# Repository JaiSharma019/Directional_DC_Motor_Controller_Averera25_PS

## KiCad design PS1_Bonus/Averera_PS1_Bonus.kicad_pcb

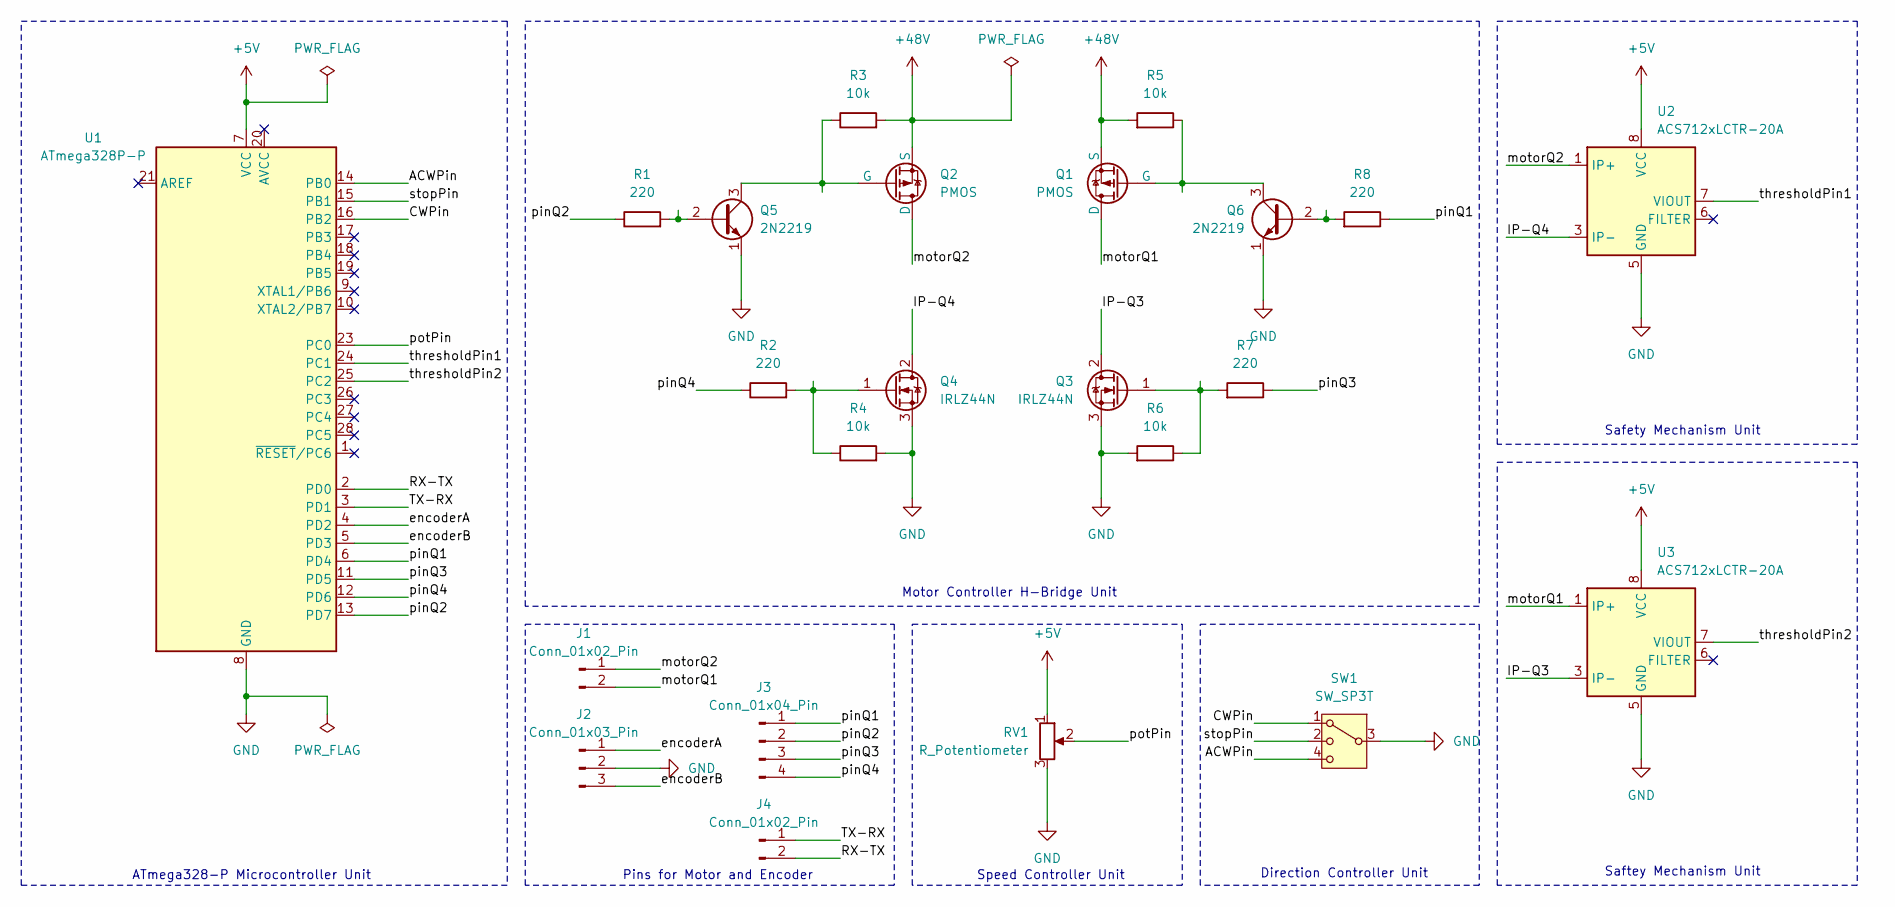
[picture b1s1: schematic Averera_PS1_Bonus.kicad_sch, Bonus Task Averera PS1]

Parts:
J1, J4: Conn_01x02_Pin; PinHeader_1x02_P2.54mm_Vertical
J2: Conn_01x03_Pin; PinHeader_1x03_P2.54mm_Vertical
J3: Conn_01x04_Pin; PinHeader_1x04_P2.54mm_Vertical
Q1, Q2: PMOS; TO-220-3_Vertical
Q3, Q4: IRLZ44N; TO-220-3_Vertical
Q5, Q6: 2N2219; TO-39-3
R1, R2, R7, R8: 220; R_Axial_DIN0207_L6.3mm_D2.5mm_P7.62mm_Horizontal
R3, R4, R5, R6: 10k; R_Axial_DIN0207_L6.3mm_D2.5mm_P7.62mm_Horizontal
RV1: R_Potentiometer; Potentiometer_Alpha_RD901F-40-15R1_Single_Vertical
SW1: SW_SP3T; SW_SP3T_PCM13
U1: ATmega328P-P; DIP-28_W7.62mm
U2, U3: ACS712xLCTR-20A; SOIC-8_3.9x4.9mm_P1.27mm

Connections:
+5V: RV1.1, U1.7 (VCC), U2.8 (VCC), U3.8 (VCC)
+48V: Q1.3 (S), Q2.3 (S), R3.2, R5.2
/ACWPin: SW1.4, U1.14 (PB0)
/CWPin: SW1.1, U1.16 (PB2)
/IP-Q3: Q3.2 (D), U3.3 (IP-), U3.4 (IP-)
/IP-Q4: Q4.2 (D), U2.3 (IP-), U2.4 (IP-)
/RX-TX: J4.2, U1.2 (PD0)
/TX-RX: J4.1, U1.3 (PD1)
/encoderA: J2.1, U1.4 (PD2)
/encoderB: J2.3, U1.5 (PD3)
/motorQ1: J1.2, Q1.1 (D), U3.1 (IP+), U3.2 (IP+)
/motorQ2: J1.1, Q2.1 (D), U2.1 (IP+), U2.2 (IP+)
/pinQ1: J3.1, R8.1, U1.6 (PD4)
/pinQ2: J3.2, R1.1, U1.13 (PD7)
/pinQ3: J3.3, R7.1, U1.11 (PD5)
/pinQ4: J3.4, R2.1, U1.12 (PD6)
/potPin: RV1.2, U1.23 (PC0)
/stopPin: SW1.2, U1.15 (PB1)
/thresholdPin1: U1.24 (PC1), U2.7 (VIOUT)
/thresholdPin2: U1.25 (PC2), U3.7 (VIOUT)
GND: J2.2, Q3.3 (S), Q4.3 (S), Q5.1 (E), Q6.1 (E), R4.2, R6.2, RV1.3, SW1.3, U1.8 (GND), U1.22 (GND), U2.5 (GND), U3.5 (GND)
unnamed: Q1.2 (G), Q6.3 (C), R5.1
unnamed: Q2.2 (G), Q5.3 (C), R3.1
unnamed: Q3.1 (G), R6.1, R7.2
unnamed: Q4.1 (G), R2.2, R4.1
unnamed: Q5.2 (B), R1.2
unnamed: Q6.2 (B), R8.2

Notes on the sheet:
Saftey Mechanism Unit
Safety Mechanism Unit
Pins for Motor and Encoder
Motor Controller H-Bridge Unit
Direction Controller Unit
ATmega328-P Microcontroller Unit
Speed Controller Unit

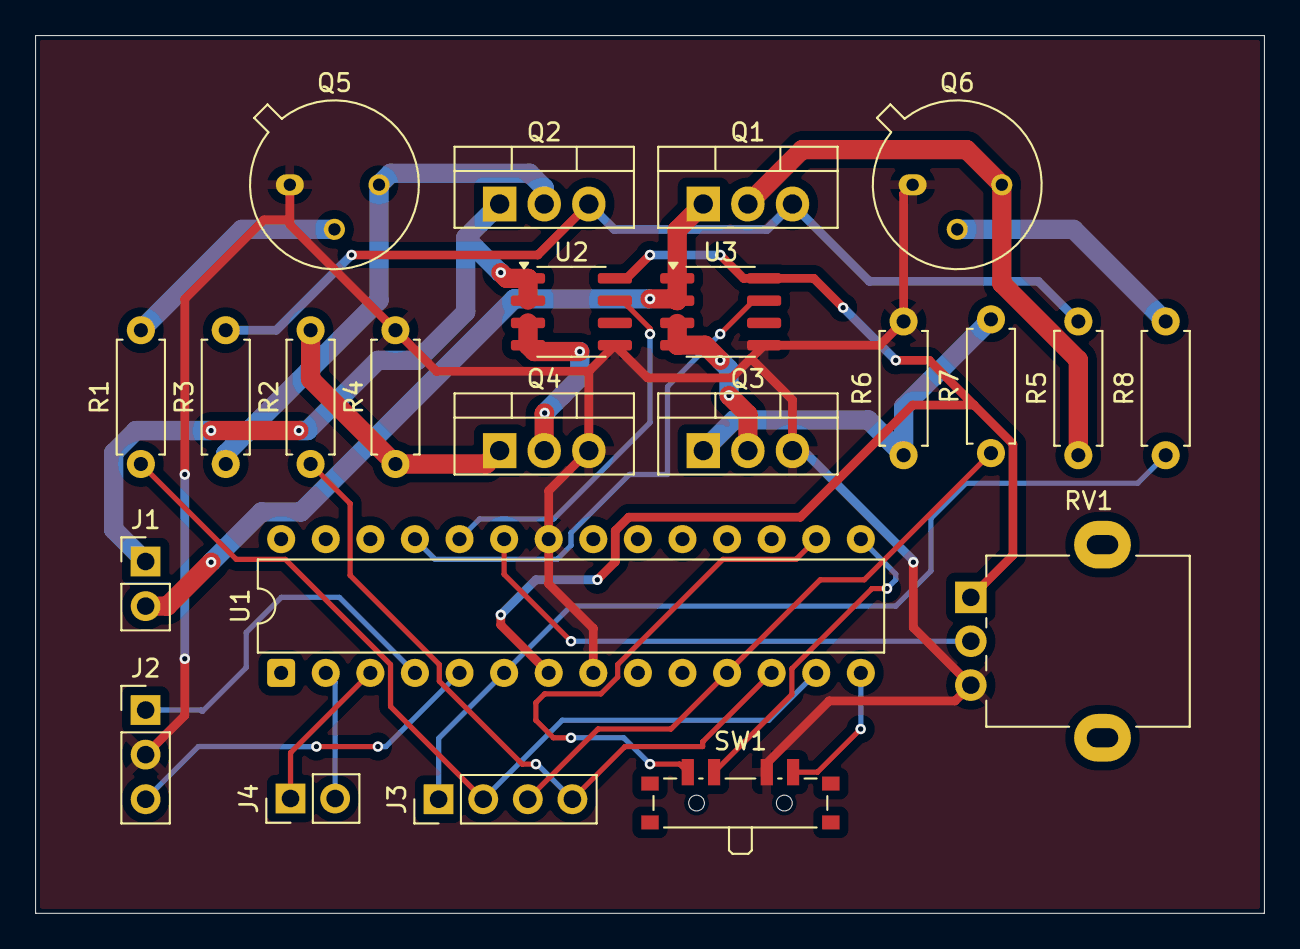
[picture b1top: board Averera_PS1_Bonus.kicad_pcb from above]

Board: 2 copper layers, 70.0 x 50.0 mm, 23 parts (0 on the bottom side), 27 nets.

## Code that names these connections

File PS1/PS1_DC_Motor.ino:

#define pinQ1 4
#define pinQ2 7
#define pinQ4 6
#define pinQ3 5
#define ACWPin 8
#define CWPin 10
#define stopPin 9
#define potPin A0
#define thresholdPin1 A1
#define thresholdPin2 A2
#define encoderA 2
#define encoderB 3
volatile long pos = 0;
unsigned long now = 0;
const int threshold = 563; // Threshold voltage = 2.5V + (2.5A)*(0.1V/A) = 2.75V
// mapping 2.75 for 1023
int pot;

void setup() {
  pinMode(pinQ1, OUTPUT);
  pinMode(pinQ2, OUTPUT);
  pinMode(pinQ3, OUTPUT);
  pinMode(pinQ4, OUTPUT);
  pinMode(encoderA, INPUT);
  pinMode(encoderB, INPUT);
  pinMode(CWPin, INPUT_PULLUP);
  pinMode(ACWPin, INPUT_PULLUP);
  pinMode(stopPin, INPUT_PULLUP);
  attachInterrupt(digitalPinToInterrupt(encoderA),encode, RISING);
  Serial.begin(9600);
  
}

void loop() {
  
  volatile bool shootThrough = false;
  
  const int interval = 100;
  Serial.print("Position: ");
  float angle = (pos*15.0);
  Serial.println(angle);

  if(millis()-now>=interval) {
    now = millis();
    if((analogRead(thresholdPin1)>threshold) || (analogRead(thresholdPin2)>threshold)) {
      shootThrough = true;
      shutDown();
      Serial.println("Status: Shoot Through");
//      delay(50);
    }
  }
  pot = analogRead(potPin);
  int PWM = map(pot, 0, 1023, 0, 255);

  
  if(digitalRead(CWPin)==LOW && shootThrough==false) {
    Serial.println("Direction: Clockwise");
    analogWrite(pinQ3, PWM);
    digitalWrite(pinQ2, HIGH);
    digitalWrite(pinQ1, LOW);
    analogWrite(pinQ4, 0);
    
  }
  else if(digitalRead(ACWPin)==LOW && shootThrough==false) {
    Serial.println("Direction: Anti-clockwise");
    analogWrite(pinQ4, PWM);
    digitalWrite(pinQ1, HIGH);
    digitalWrite(pinQ2, LOW);
    analogWrite(pinQ3, 0);
    
    
  }
  else if(digitalRead(stopPin)==LOW && shootThrough==false) {
    Serial.println("Status: Stopped");
    shutDown();
    
  }
}
  

  

void encode() {
  if(digitalRead(stopPin)==HIGH) {
  int b = digitalRead(encoderB);
//  int a = digitalRead(encoderA);
  if( b==HIGH) {
    pos++;
    
  }
  else {
    pos--;
    
  }

  }
}

void shutDown() {
  digitalWrite(pinQ1, LOW);
  digitalWrite(pinQ2, LOW);
  digitalWrite(pinQ3, HIGH);
  digitalWrite(pinQ4, HIGH);
  
}

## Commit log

2026-03-08 Uploaded PS1 simulation and report files
2026-03-08 Uploaded the Arduino code
2026-03-08 Uploaded PS2 simulation and report files
2026-03-08 Uploaded PS2 Arduino code
2026-03-08 Uploaded the PS1 Bonus KiCAD files
2026-03-08 Uploaded Gerber zip file
2026-03-08 Uploaded custom THT potentiometer footprint
